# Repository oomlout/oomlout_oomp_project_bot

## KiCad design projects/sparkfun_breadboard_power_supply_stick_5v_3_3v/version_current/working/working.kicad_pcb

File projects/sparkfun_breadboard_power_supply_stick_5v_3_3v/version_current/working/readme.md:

# Breadboard_Power_Supply_Stick_5V-3.3V by sparkfun  
This is a harvested standardized copy of a project from github.  
The original project can be found at:  
https://github.com/sparkfun/Breadboard_Power_Supply_Stick_5V-3.3V  
Please consult that link for additional, details, files, and license information.  
Note: It was auto harvested and if the original repo had more than one board file or anything out of the ordinary the files here are likely not representative.

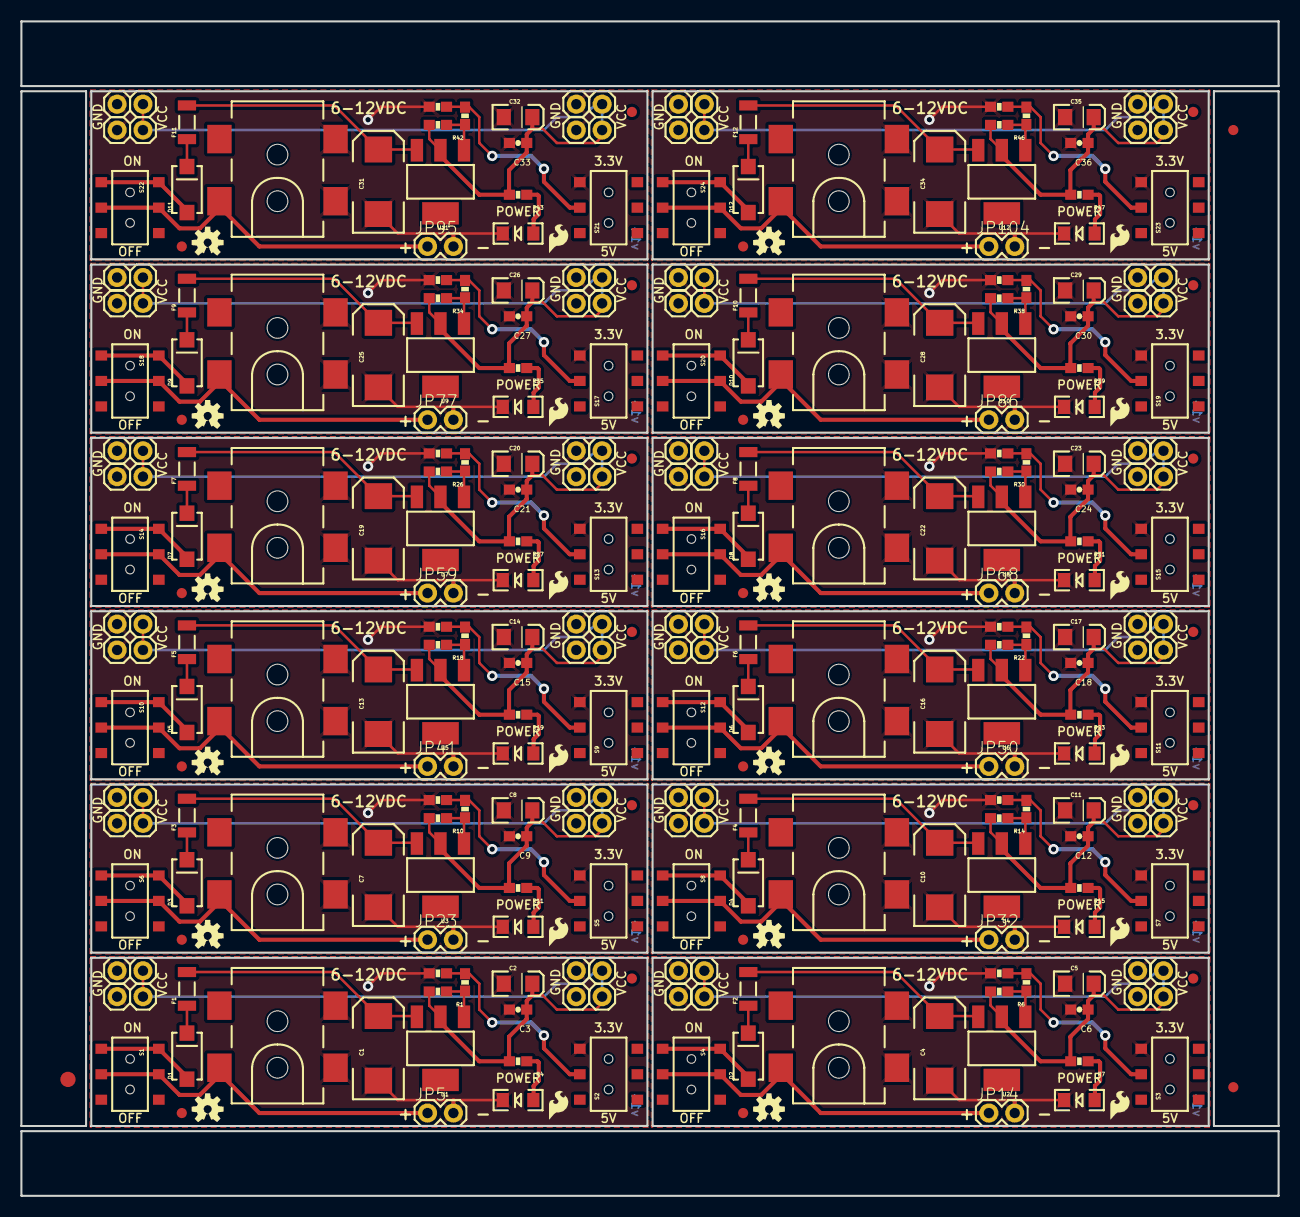
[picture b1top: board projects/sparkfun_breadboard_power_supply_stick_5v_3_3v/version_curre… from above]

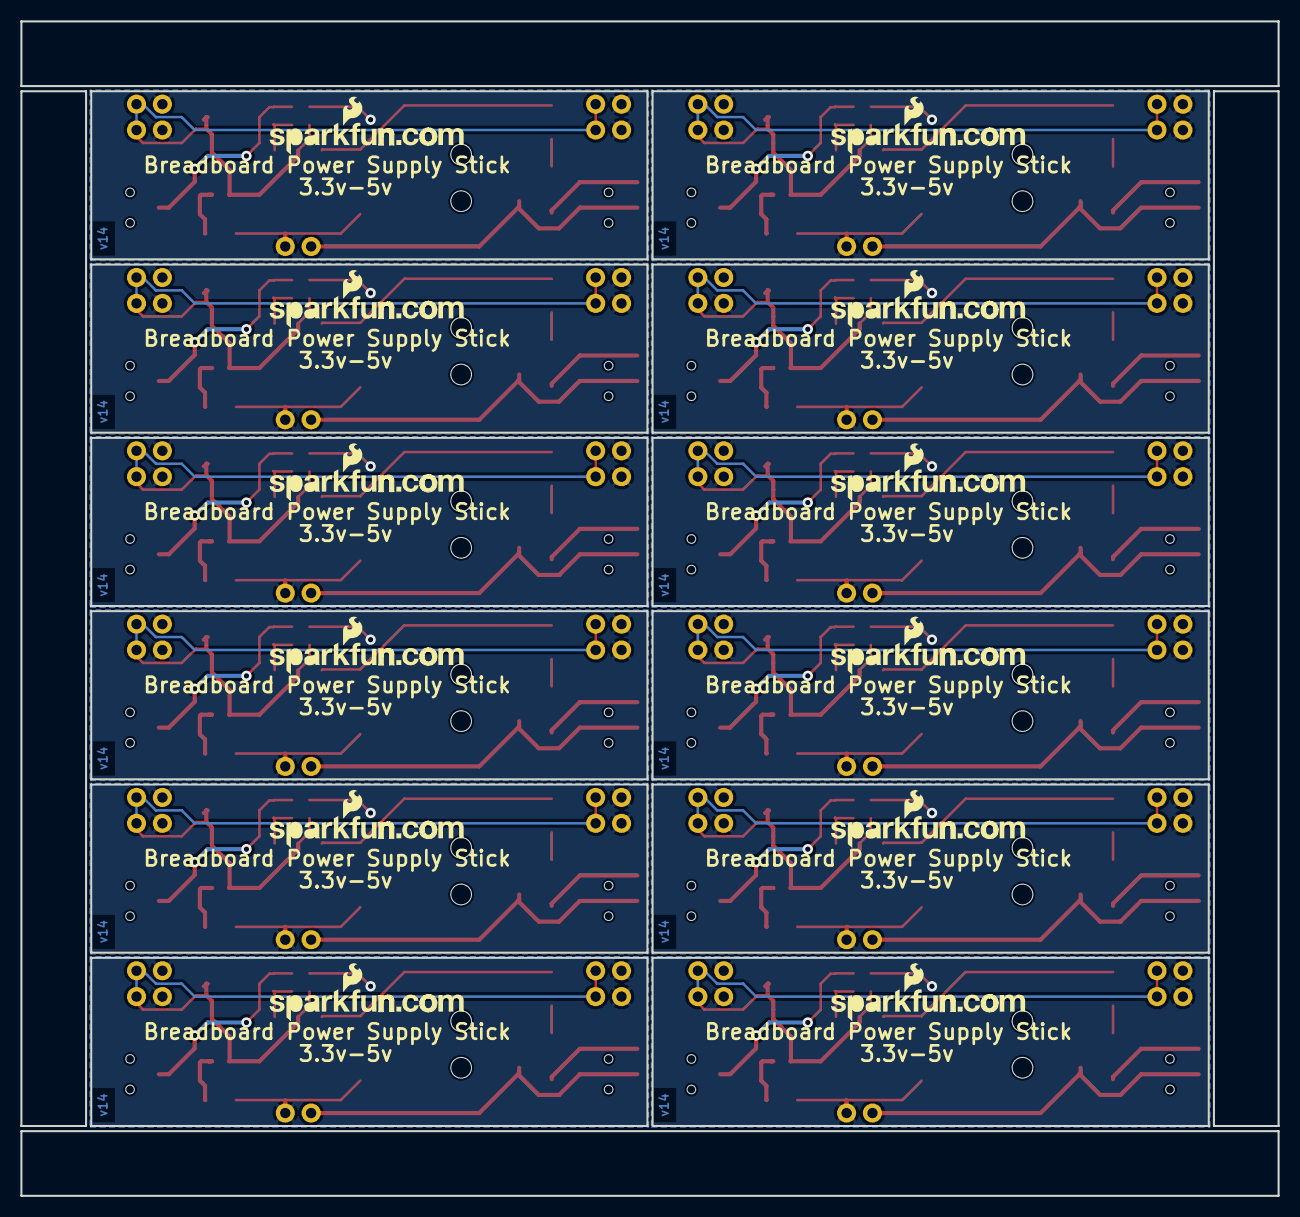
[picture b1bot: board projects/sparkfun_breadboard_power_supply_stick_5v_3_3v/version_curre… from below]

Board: 2 copper layers, 123.4 x 115.3 mm, 339 parts (12 on the bottom side), 108 nets.

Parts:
C1, C4, C7, C10, C13, C16, C19, C22, C25, C28, C31, C34: 100uF; EIA7343
C2, C5, C8, C11, C14, C17, C20, C23, C26, C29, C32, C35: 10uF; EIA3216
C3, C6, C9, C12, C15, C18, C21, C24, C27, C30, C33, C36: 0.1uF; 0603-CAP
D1, D2, D3, D4, D5, D6, D7, D8, D9, D10, D11, D12: 1N4001; SMA-DIODE-TYLERALT1
E$1: FIDUCIAL-1.5X3
E$4, E$6: FIDUCIAL-1X2
F1, F2, F3, F4, F5, F6, F7, F8, F9, F10, F11, F12: PTCSMD-W; PTC-1206-WIDE
J1, J2, J3, J4, J5, J6, J7, J8, J9, J10, J11, J12: 5.5x2.1mm Barrel; POWER_JACK_SMD
JP1, JP2, JP3, JP4, JP6, JP7, JP8, JP9, JP10, JP11, JP12, JP13, JP15, JP16, JP17, JP18, JP19, JP20, JP21, JP22, JP24, JP25, JP26, JP27, JP28, JP29, JP30, JP31, JP33, JP34, JP35, JP36, JP37, JP38, JP39, JP40, JP42, JP43, JP44, JP45, JP46, JP47, JP48, JP49, JP51, JP52, JP53, JP54, JP55, JP56, JP57, JP58, JP60, JP61, JP62, JP63, JP64, JP65, JP66, JP67, JP69, JP70, JP71, JP72, JP73, JP74, JP75, JP76, JP78, JP79, JP80, JP81, JP82, JP83, JP84, JP85, JP87, JP88, JP89, JP90, JP91, JP92, JP93, JP94, JP96, JP97, JP98, JP99, JP100, JP101, JP102, JP103, JP105, JP106, JP107, JP108: M01PTH; 1X01
JP5, JP14, JP23, JP32, JP41, JP50, JP59, JP68, JP77, JP86, JP95, JP104: 1X02
LED1, LED2, LED3, LED4, LED5, LED6, LED7, LED8, LED9, LED10, LED11, LED12: Power; LED-1206
LOGO1, LOGO2, LOGO3, LOGO4, LOGO5, LOGO6, LOGO7, LOGO8, LOGO9, LOGO10, LOGO11, LOGO12: OSHW-LOGOS; OSHW-LOGO-S
R1, R6, R10, R14, R18, R22, R26, R30, R34, R38, R42, R46: 240; 0603-RES
R2, R5, R9, R13, R17, R21, R25, R29, R33, R37, R41, R45: 390; 0603-RES
R3, R4, R7, R8, R11, R12, R15, R16, R19, R20, R23, R24, R27, R28, R31, R32, R35, R36, R39, R40, R43, R44, R47, R48: 330; 0603-RES
S1, S4, S6, S8, S10, S12, S14, S16, S18, S20, S22, S24: On/Off; AYZ0202
S2, S3, S5, S7, S9, S11, S13, S15, S17, S19, S21, S23: Voltage; AYZ0202
U1, U2, U3, U4, U5, U6, U7, U8, U9, U10, U11, U12: V_REG_317SMD; SOT223
U$1, U$5, U$9, U$13, U$17, U$21, U$25, U$29, U$33, U$37, U$41, U$45: LOGO-SFESK; SFE-LOGO-FLAME
U$2, U$6, U$10, U$14, U$18, U$22, U$26, U$30, U$34, U$38, U$42, U$46: LOGO-SFENEW; SFE-NEW-WEBLOGO
U$3, U$4, U$7, U$8, U$11, U$12, U$15, U$16, U$19, U$20, U$23, U$24, U$27, U$28, U$31, U$32, U$35, U$36, U$39, U$40, U$43, U$44, U$47, U$48: FIDUCIAL1X2; FIDUCIAL-1X2

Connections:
GND: C1.C, C2.C, C3.2, J1.GND, J1.P$4, JP1.1, JP4.1, JP5.2, JP6.1, JP9.1, LED2.C, R3.1, S2.3
GND1: C4.C, C5.C, C6.2, J2.GND, J2.P$4, JP10.1, JP13.1, JP14.2, JP15.1, JP18.1, LED1.C, R8.1, S3.3
GND2: C7.C, C8.C, C9.2, J3.GND, J3.P$4, JP19.1, JP22.1, JP23.2, JP24.1, JP27.1, LED3.C, R12.1, S5.3
GND3: C10.C, C11.C, C12.2, J4.GND, J4.P$4, JP28.1, JP31.1, JP32.2, JP33.1, JP36.1, LED4.C, R16.1, S7.3
GND4: C13.C, C14.C, C15.2, J5.GND, J5.P$4, JP37.1, JP40.1, JP41.2, JP42.1, JP45.1, LED5.C, R20.1, S9.3
GND5: C16.C, C17.C, C18.2, J6.GND, J6.P$4, JP46.1, JP49.1, JP50.2, JP51.1, JP54.1, LED6.C, R24.1, S11.3
GND6: C19.C, C20.C, C21.2, J7.GND, J7.P$4, JP55.1, JP58.1, JP59.2, JP60.1, JP63.1, LED7.C, R28.1, S13.3
GND7: C22.C, C23.C, C24.2, J8.GND, J8.P$4, JP64.1, JP67.1, JP68.2, JP69.1, JP72.1, LED8.C, R32.1, S15.3
GND8: C25.C, C26.C, C27.2, J9.GND, J9.P$4, JP73.1, JP76.1, JP77.2, JP78.1, JP81.1, LED9.C, R36.1, S17.3
GND9: C28.C, C29.C, C30.2, J10.GND, J10.P$4, JP82.1, JP85.1, JP86.2, JP87.1, JP90.1, LED10.C, R40.1, S19.3
GND10: C31.C, C32.C, C33.2, J11.GND, J11.P$4, JP91.1, JP94.1, JP95.2, JP96.1, JP99.1, LED11.C, R44.1, S21.3
GND11: C34.C, C35.C, C36.2, J12.GND, J12.P$4, JP100.1, JP103.1, JP104.2, JP105.1, JP108.1, LED12.C, R48.1, S23.3
unnamed: D1.C, F1.1
unnamed: D1.A, S1.1, S1.4
unnamed: R5.2, R6.1, U2.1
unnamed: R2.1, R3.2, S2.2
unnamed: R1.1, R2.2, U1.1
unnamed: LED1.A, R7.1
unnamed: D2.C, F2.1
unnamed: LED2.A, R4.1
unnamed: D2.A, S4.1, S4.4
unnamed: R5.1, R8.2, S3.2
unnamed: R9.2, R10.1, U3.1
unnamed: LED3.A, R11.1
unnamed: D3.C, F3.1
unnamed: D3.A, S6.1, S6.4
unnamed: R9.1, R12.2, S5.2
unnamed: R13.2, R14.1, U4.1
unnamed: LED4.A, R15.1
unnamed: D4.C, F4.1
unnamed: D4.A, S8.1, S8.4
unnamed: R13.1, R16.2, S7.2
unnamed: R17.2, R18.1, U5.1
unnamed: LED5.A, R19.1
unnamed: D5.C, F5.1
unnamed: D5.A, S10.1, S10.4
unnamed: R17.1, R20.2, S9.2
unnamed: R21.2, R22.1, U6.1
unnamed: LED6.A, R23.1
unnamed: D6.C, F6.1
unnamed: D6.A, S12.1, S12.4
unnamed: R21.1, R24.2, S11.2
unnamed: R25.2, R26.1, U7.1
unnamed: LED7.A, R27.1
unnamed: D7.C, F7.1
unnamed: D7.A, S14.1, S14.4
unnamed: R25.1, R28.2, S13.2
unnamed: R29.2, R30.1, U8.1
unnamed: LED8.A, R31.1
unnamed: D8.C, F8.1
unnamed: D8.A, S16.1, S16.4
unnamed: R29.1, R32.2, S15.2
unnamed: R33.2, R34.1, U9.1
unnamed: LED9.A, R35.1
unnamed: D9.C, F9.1
unnamed: D9.A, S18.1, S18.4
unnamed: R33.1, R36.2, S17.2
unnamed: R37.2, R38.1, U10.1
unnamed: LED10.A, R39.1
unnamed: D10.C, F10.1
unnamed: D10.A, S20.1, S20.4
unnamed: R37.1, R40.2, S19.2
unnamed: R41.2, R42.1, U11.1
unnamed: LED11.A, R43.1
unnamed: D11.C, F11.1
unnamed: D11.A, S22.1, S22.4
unnamed: R41.1, R44.2, S21.2
unnamed: R45.2, R46.1, U12.1
unnamed: LED12.A, R47.1
unnamed: D12.C, F12.1
unnamed: D12.A, S24.1, S24.4
unnamed: R45.1, R48.2, S23.2
RAW: C1.A, F1.2, U1.3
RAW1: C4.A, F2.2, U2.3
RAW2: C7.A, F3.2, U3.3
RAW3: C10.A, F4.2, U4.3
RAW4: C13.A, F5.2, U5.3
RAW5: C16.A, F6.2, U6.3
RAW6: C19.A, F7.2, U7.3
RAW7: C22.A, F8.2, U8.3
RAW8: C25.A, F9.2, U9.3
RAW9: C28.A, F10.2, U10.3
RAW10: C31.A, F11.2, U11.3
RAW11: C34.A, F12.2, U12.3
VCC: C2.A, C3.1, JP2.1, JP3.1, JP7.1, JP8.1, R1.2, R4.2, U1.2
VCC1: C5.A, C6.1, JP11.1, JP12.1, JP16.1, JP17.1, R6.2, R7.2, U2.2
VCC2: C8.A, C9.1, JP20.1, JP21.1, JP25.1, JP26.1, R10.2, R11.2, U3.2
VCC3: C11.A, C12.1, JP29.1, JP30.1, JP34.1, JP35.1, R14.2, R15.2, U4.2
VCC4: C14.A, C15.1, JP38.1, JP39.1, JP43.1, JP44.1, R18.2, R19.2, U5.2
VCC5: C17.A, C18.1, JP47.1, JP48.1, JP52.1, JP53.1, R22.2, R23.2, U6.2
VCC6: C20.A, C21.1, JP56.1, JP57.1, JP61.1, JP62.1, R26.2, R27.2, U7.2
VCC7: C23.A, C24.1, JP65.1, JP66.1, JP70.1, JP71.1, R30.2, R31.2, U8.2
VCC8: C26.A, C27.1, JP74.1, JP75.1, JP79.1, JP80.1, R34.2, R35.2, U9.2
VCC9: C29.A, C30.1, JP83.1, JP84.1, JP88.1, JP89.1, R38.2, R39.2, U10.2
VCC10: C32.A, C33.1, JP92.1, JP93.1, JP97.1, JP98.1, R42.2, R43.2, U11.2
VCC11: C35.A, C36.1, JP101.1, JP102.1, JP106.1, JP107.1, R46.2, R47.2, U12.2
VIN: J1.VIN0, JP5.1, S1.2, S1.5
VIN1: J2.VIN0, JP14.1, S4.2, S4.5
VIN2: J3.VIN0, JP23.1, S6.2, S6.5
VIN3: J4.VIN0, JP32.1, S8.2, S8.5
VIN4: J5.VIN0, JP41.1, S10.2, S10.5
VIN5: J6.VIN0, JP50.1, S12.2, S12.5
VIN6: J7.VIN0, JP59.1, S14.2, S14.5
VIN7: J8.VIN0, JP68.1, S16.2, S16.5
VIN8: J9.VIN0, JP77.1, S18.2, S18.5
VIN9: J10.VIN0, JP86.1, S20.2, S20.5
VIN10: J11.VIN0, JP95.1, S22.2, S22.5
VIN11: J12.VIN0, JP104.1, S24.2, S24.5

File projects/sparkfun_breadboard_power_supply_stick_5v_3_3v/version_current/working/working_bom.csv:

Row,Description,Part,References,Value,Footprint,Quantity Per PCB,Status,Datasheet
1,,CAP0603-CAP,C3,0.1uF,0603-CAP,1, ,
2,,CAP_POL1206,C2,10uF,EIA3216,1, ,
3,,CAP_POL7343,C1,100uF,EIA7343,1, ,
4,,DIODESMA-TYLERALT1,D1,1N4001,SMA-DIODE-TYLERALT1,1, ,
5,,PTCSMD-W,F1,PTCSMD-W,PTC-1206-WIDE,1, ,
6,,FRAME-LETTER,FRAME1,FRAME-LETTER,CREATIVE_COMMONS,1, ,
7,,POWER_JACKSMD,J1,POWER_JACKSMD,POWER_JACK_SMD,1, ,
8,,M01PTH,JP1 JP2 JP3 JP4 JP6 JP7 JP8 JP9,M01PTH,1X01,8, ,
9,,M02PTH,JP5,M02PTH,1X02,1, ,
10,,LED1206,LED2,Power,LED-1206,1, ,
11,,OSHW-LOGOS,LOGO1,OSHW-LOGOS,OSHW-LOGO-S,1, ,
12,,RESISTOR0603-RES,R1,240,0603-RES,1, ,
13,,RESISTOR0603-RES,R3 R4,330,0603-RES,2, ,
14,,RESISTOR0603-RES,R2,390,0603-RES,1, ,
15,,AYZ0202,S1,AYZ0202,AYZ0202,1, ,
16,,SWITCH-SPSTSMD,S2,Voltage,AYZ0202,1, ,
17,,V_REG_317SMD,U1,V_REG_317SMD,SOT223,1, ,
18,,LOGO-SFENEW,U$2,LOGO-SFENEW,SFE-NEW-WEBLOGO,1, ,
19,,LOGO-SFESK,U$1,LOGO-SFESK,SFE-LOGO-FLAME,1, ,





Project info:
Schematic:,working
Variant:,default
Revision:,
Date:,2023-08-06_12-56-00
KiCad Version:,7.0.6-7.0.6~ubuntu22.04.1
Statistics:
Component Groups:,19
Component Count:,27 (0 SMD/ 0 THT)
Fitted Components:,27 (0 SMD/ 0 THT)
Number of PCBs:,1
Total Components:,27

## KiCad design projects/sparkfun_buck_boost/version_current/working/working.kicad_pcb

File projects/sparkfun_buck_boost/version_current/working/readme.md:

# Buck-Boost by sparkfun  
This is a harvested standardized copy of a project from github.  
The original project can be found at:  
https://github.com/sparkfun/Buck-Boost  
Please consult that link for additional, details, files, and license information.  
Note: It was auto harvested and if the original repo had more than one board file or anything out of the ordinary the files here are likely not representative.

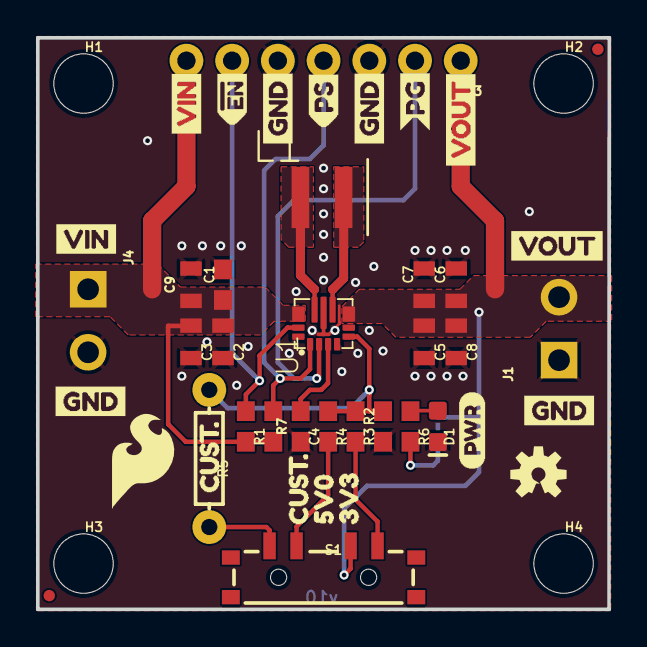
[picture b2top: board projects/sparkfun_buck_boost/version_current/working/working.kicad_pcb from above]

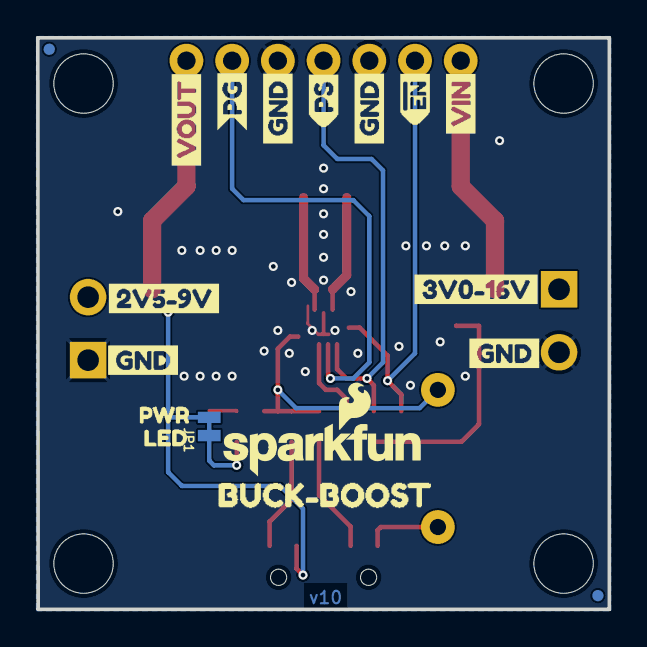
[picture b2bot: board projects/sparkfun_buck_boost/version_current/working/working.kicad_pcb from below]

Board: 2 copper layers, 31.8 x 31.8 mm, 67 parts (18 on the bottom side), 15 nets.

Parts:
C1, C4: 0.1uF; 0603
C2, C3, C5, C9: 10uF; 0805
C6, C7, C8: 22uF; 0805
D1: RED; LED-0603
FD1, FD2, FD3, FD4: FIDUCIALUFIDUCIAL; FIDUCIAL-MICRO
FRAME1: FRAME-LETTER; CREATIVE_COMMONS
H1, H2, H3, H4: STAND-OFF
J1, J4: SCREWTERMINAL-3.5MM-2-NS
J3: 1X07_NO_SILK
JP1: SMT-JUMPER_2_NC_TRACE_NO-SILK
L1: 1.5uH; XFL4020
LOGO1: SFE_LOGO_NAME_FLAME.1_INCH; SFE_LOGO_NAME_FLAME_.1
LOGO2: OSHW-LOGOS; OSHW-LOGO-S
LOGO3: SPECIAL_INSTRUCTIONS-ORDERING; ORDERING_INSTRUCTIONS
R1, R7: 10k; 0603
R2: 68.1k; 0603
R3: 213k; 0603
R4: 365k; 0603
R5: CUSTOM; AXIAL-0.3
R6: 1k; 0603
S1: SWITCH_SP3T_SMD
U1: TPS63070; VQFN-15-HR(3X2.5)
U$1: PWR2
U$2, U$17: CUST#7
U$3, U$25: VIN0
U$4, U$20, U$30, U$31: GND1
U$5: VIN3
U$6, U$7, U$12, U$13: GND4
U$8: VOUT5
U$9: SFE_LOGO_FLAME_.2
U$10: 3V0#16V6
U$11: PWR1
U$14: 2V5#9V1
U$15: BUCK#BOOST18
U$16: LED0
U$18: 5V08
U$19: 3V39
U$21, U$26: VOUT2
U$22, U$28: #EN0
U$23, U$29: PS1
U$24, U$27: PG2

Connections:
FB: R2.2, R3.1, R4.1, R5.P$1, U1.P$5
GND: C1.2, C2.2, C3.2, C4.2, C5.2, C6.2, C7.2, C8.2, C9.2, D1.C, J1.1, J3.3, J3.5, J4.2, R2.1, U1.P$4, U1.P$6, U1.P$10, U1.P$15
unnamed: L1.P$1, U1.P$11
unnamed: L1.P$2, U1.P$9
unnamed: R5.P$2, S1.1
unnamed: R4.2, S1.2
unnamed: C4.1, U1.P$3
unnamed: R3.2, S1.4
unnamed: JP1.1, R6.2
unnamed: D1.A, R6.1
PG: J3.2, U1.P$2
PS: J3.4, R7.1, U1.P$1
VIN: C1.1, C2.1, C3.1, C9.1, J3.7, J4.1, R1.2, R7.2, U1.P$12/13
VOUT: C5.1, C6.1, C7.1, C8.1, J1.2, J3.1, JP1.2, S1.3, U1.P$7/8
~EN: J3.6, R1.1, U1.P$14

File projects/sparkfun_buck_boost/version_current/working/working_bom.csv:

"Id";"Designator";"Footprint";"Quantity";"Designation";"Supplier and ref";
1;"U$21,U$26";"VOUT2";2;"";;;
2;"C8,C6,C7";"0805";3;"22uF";;;
3;"LOGO2";"OSHW-LOGO-S";1;"OSHW-LOGOS";;;
4;"C9,C2,C3,C5";"0805";4;"10uF";;;
5;"U$20,U$4,U$30,U$31";"GND1";4;"";;;
6;"J1,J4";"SCREWTERMINAL-3.5MM-2-NS";2;"";;;
7;"C4,C1";"0603";2;"0.1uF";;;
8;"L1";"XFL4020";1;"1.5uH";;;
9;"U$23,U$29";"PS1";2;"";;;
10;"R4";"0603";1;"365k";;;
11;"U$7,U$6,U$13,U$12";"GND4";4;"";;;
12;"FD3,FD1,FD2,FD4";"FIDUCIAL-MICRO";4;"FIDUCIALUFIDUCIAL";;;
13;"FRAME1";"CREATIVE_COMMONS";1;"FRAME-LETTER";;;
14;"H3,H2,H1,H4";"STAND-OFF";4;"STAND-OFF";;;
15;"U$8";"VOUT5";1;"";;;
16;"R5";"AXIAL-0.3";1;"CUSTOM";;;
17;"U$2,U$17";"CUST#7";2;"";;;
18;"U$18";"5V08";1;"";;;
19;"U1";"VQFN-15-HR(3X2.5)";1;"TPS63070";;;
20;"U$19";"3V39";1;"";;;
21;"D1";"LED-0603";1;"RED";;;
22;"R2";"0603";1;"68.1k";;;
23;"LOGO3";"ORDERING_INSTRUCTIONS";1;"SPECIAL_INSTRUCTIONS-ORDERING";;;
24;"R3";"0603";1;"213k";;;
25;"U$3,U$25";"VIN0";2;"";;;
26;"R6";"0603";1;"1k";;;
27;"U$5";"VIN3";1;"";;;
28;"S1";"SWITCH_SP3T_SMD";1;"";;;
29;"R7,R1";"0603";2;"10k";;;
30;"U$9";"SFE_LOGO_FLAME_.2";1;"";;;
31;"J3";"1X07_NO_SILK";1;"";;;
32;"U$1";"PWR2";1;"";;;
33;"U$24,U$27";"PG2";2;"";;;
34;"U$22,U$28";"#EN0";2;"";;;
35;"U$16";"LED0";1;"";;;
36;"JP1";"SMT-JUMPER_2_NC_TRACE_NO-SILK";1;"";;;
37;"LOGO1";"SFE_LOGO_NAME_FLAME_.1";1;"SFE_LOGO_NAME_FLAME.1_INCH";;;
38;"U$10";"3V0#16V6";1;"";;;
39;"U$11";"PWR1";1;"";;;
40;"U$15";"BUCK#BOOST18";1;"";;;
41;"U$14";"2V5#9V1";1;"";;;

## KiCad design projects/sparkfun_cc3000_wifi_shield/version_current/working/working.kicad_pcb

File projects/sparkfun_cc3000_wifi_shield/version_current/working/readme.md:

# OOMP Project  
## CC3000_WiFi_Shield  by sparkfun  
  
oomp key: oomp_projects_flat_sparkfun_cc3000_wifi_shield  
(snippet of original readme)  
  
CC3000_WiFi_Shield  
====================  
  
[    
*CC3000 WiFi Shield (WRL-12071)*](https://www.sparkfun.com/products/12071)  
  
Arduino WiFi shield for the [TI CC3000 module](http://www.ti.com/product/cc3000). The datasheet can be found [here](http://www.ti.com/lit/ds/symlink/cc3000.pdf).  
  
Arduino library and examples can be found in the [SFE_CC3000_Library](https://github.com/sparkfun/SFE_CC3000_Library).  
  
This part was created in Eagle v6.5.0. Example sketches were created in Arduino v1.0.5.  
  
Repository Contents  
-------------------  
  
* **/Hardware** - All Eagle design files (.brd, .sch, .STL)  
* **/Production** - Test bed files and production panel files  
  
Version History  
---------------  
* **v1.0** Initial release  
  
License Information  
-------------------  
The hardware is released under [Creative Commons Share-alike 3.0](http://creativecommons.org/licenses/by-sa/3.0/).    
All other code is open source so please feel free to do anything you want with it; you buy me a beer if you use this and we meet someday ([Beerware license](http://en.wikipedia.org/wiki/Beerware)).  
  full source readme at [readme_src.md](readme_src.md)  
  
source repo at: [https://github.com/sparkfun/CC3000_WiFi_Shield](https://github.com/sparkfun/CC3000_WiFi_Shield)  
## Board  

## Schematic  

[schematic pdf](working_schematic.pdf)  
## Images

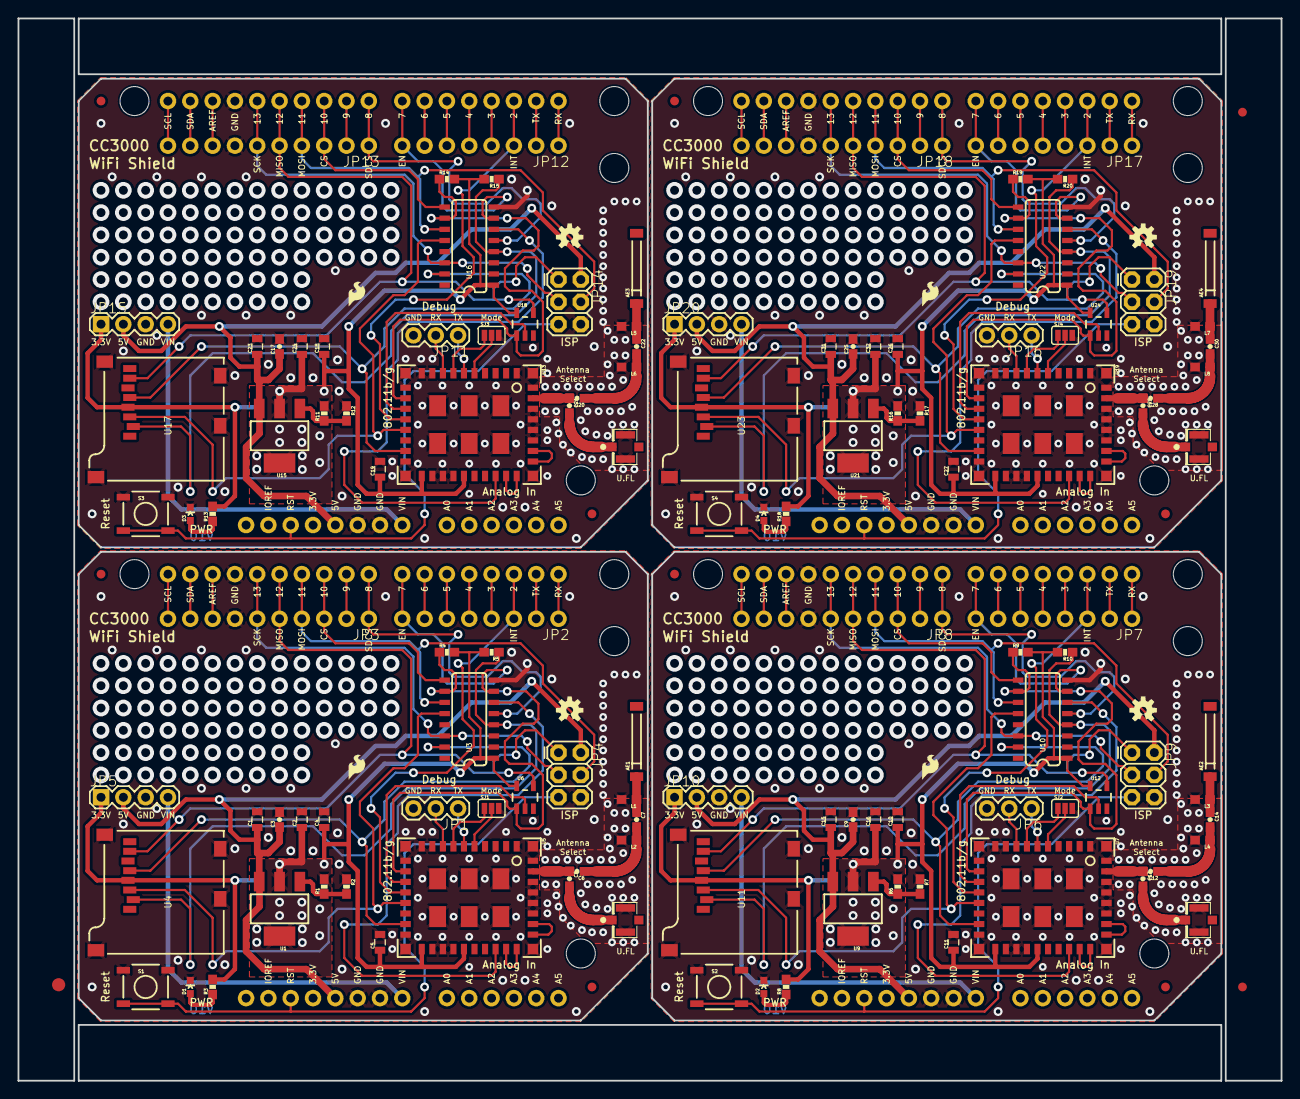
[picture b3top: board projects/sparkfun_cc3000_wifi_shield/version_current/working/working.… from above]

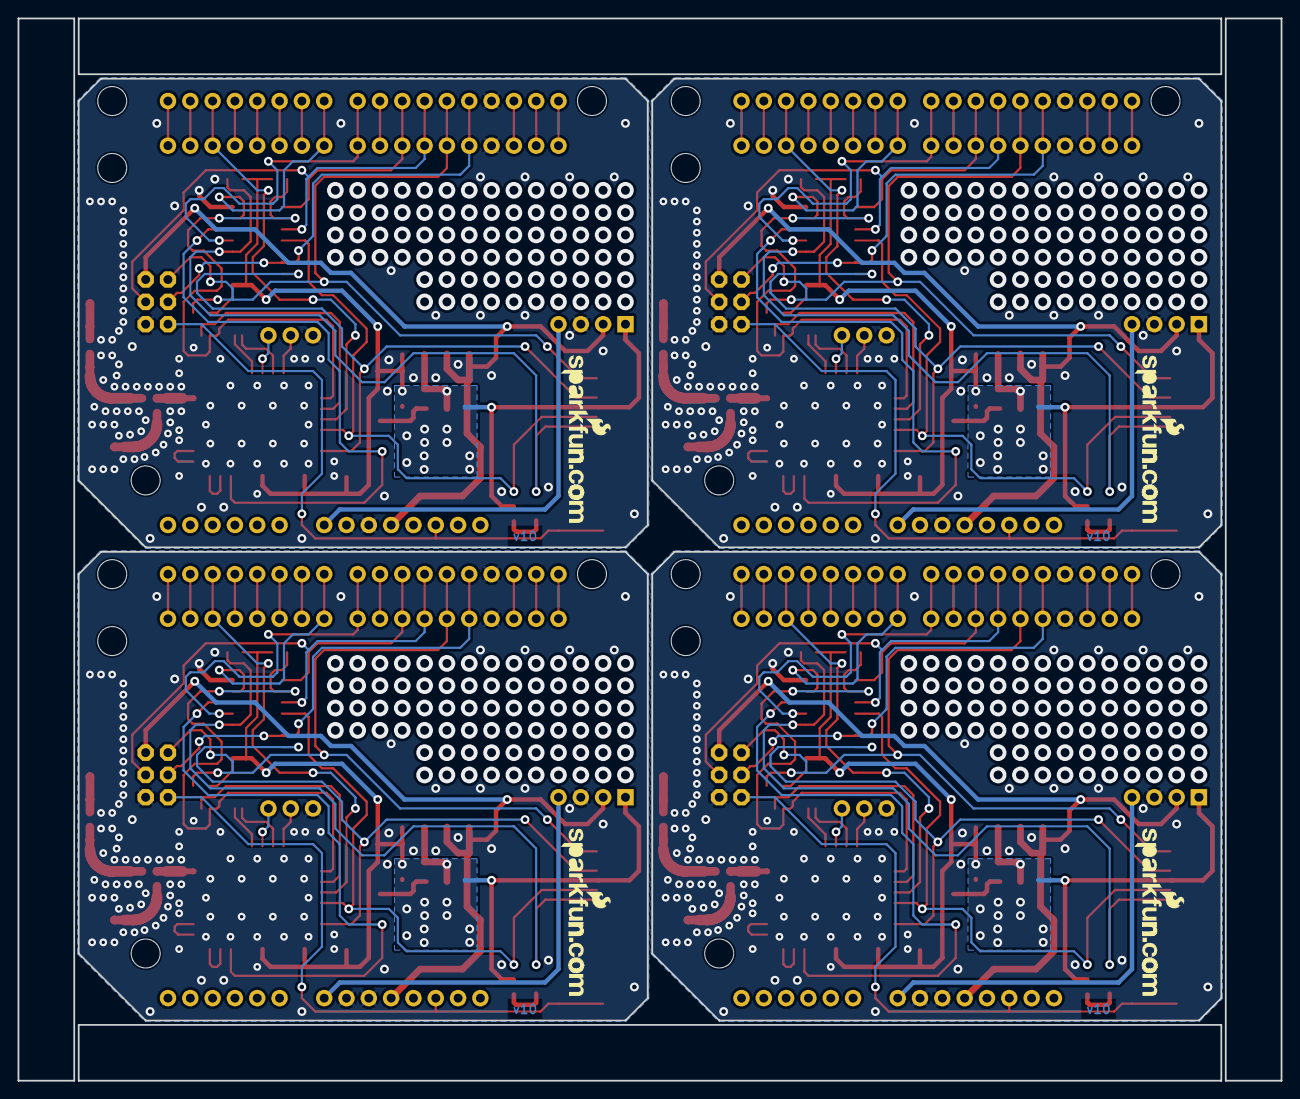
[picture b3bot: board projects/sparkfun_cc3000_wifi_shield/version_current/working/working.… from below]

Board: 4 copper layers, 143.8 x 120.9 mm, 163 parts (4 on the bottom side), 160 nets.

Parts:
@HOLE0, @HOLE1, @HOLE2, @HOLE3, @HOLE4, @HOLE5, @HOLE6, @HOLE7: (no value)
AE1, AE2, AE3, AE4: ANTENNA22500AT44M0400; ANTENNA-CHIP_2500AT44M0400
C1, C2, C15, C16, C23, C24, C31, C32: 10uF; 0805
C3, C9, C17, C25: 0.1uF; 0603-CAP
C4, C5, C10, C11, C18, C19, C26, C27: 1uF; 0805
C6, C12, C20, C28: 10pF; 0603-CAP
C7, C14, C22, C30: 2.2pF; 0603-CAP
C8, C13, C21, C29: DNP; 0603-CAP
D1, D2, D3, D4: GREEN; LED-0603
E$1: FIDUCIAL-1.5X3
E$4, E$5: FIDUCIAL-1X2
FID1, FID2, FID3, FID4, FID5, FID6, FID7, FID8: FIDUCIAL1X2; FIDUCIAL-1X2
J1, J2, J3, J4: U.FL
JP1, JP6, JP11, JP16: Debug; 1X03
JP2, JP7, JP12, JP17: 1X08_NO_SILK
JP3, JP8, JP13, JP18: M10NO_SILK; 1X10_NO_SILK
JP4, JP9, JP14, JP19: AVR_SPI_PRG_6PTH; 2X3
JP5, JP10, JP15, JP20: 1X04
L1, L3, L5, L7: DNP; 0603
L2, L4, L6, L8: 2.2nH; 0603
LOGO1, LOGO4, LOGO7, LOGO10: OSHW-LOGOS; OSHW-LOGO-S
LOGO2, LOGO5, LOGO8, LOGO11: LOGO-SFENEW; SFE-NEW-WEBLOGO
LOGO3, LOGO6, LOGO9, LOGO12: LOGO-SFESK; SFE-LOGO-FLAME
R1, R6, R11, R16: 240; 0603-RES
R2, R3, R7, R8, R12, R13, R17, R18: 390; 0603-RES
R4, R5, R9, R10, R14, R15, R19, R20: 10k; 0603-RES
S1, S2, S3, S4: RESET; TACTILE_SWITCH_SMD
SJ1, SJ2, SJ3, SJ4: Mode; SJ_3_PASTE1&2
STANDOFF1, STANDOFF2, STANDOFF3, STANDOFF4, STANDOFF5, STANDOFF6, STANDOFF7, STANDOFF8: STAND-OFF
U1, U9, U15, U21: LM1117; SOT223
U2, U8, U14, U20: ARDUINO_R3_SHIELDNOLABELS; UNO_R3_SHIELD_NOLABELS
U3, U10, U16, U22: 74HC4050; SO016
U4, U11, U17, U23: USD-SOCKETNEW; MICRO-SD-SOCKET-PP
U5, U7, U13, U19: CC3000; QFN-46_CC3000
U6, U12, U18, U24: 74AHC1G125; SOT23-5

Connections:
3.3V: C2.1, C4.1, C5.1, JP5.1, R1.2, R3.2, R4.2, R5.2, U1.2, U1.4, U3.1, U4.4, U5.P$19, U5.P$23, U6.5
3.3V1: C10.1, C11.1, C16.1, JP10.1, R6.2, R8.2, R9.2, R10.2, U7.P$19, U7.P$23, U9.2, U9.4, U10.1, U11.4, U12.5
3.3V2: C18.1, C19.1, C24.1, JP15.1, R11.2, R13.2, R14.2, R15.2, U13.P$19, U13.P$23, U15.2, U15.4, U16.1, U17.4, U18.5
3.3V3: C26.1, C27.1, C32.1, JP20.1, R16.2, R18.2, R19.2, R20.2, U19.P$19, U19.P$23, U21.2, U21.4, U22.1, U23.4, U24.5
5V: C1.1, C3.1, JP4.2, JP5.2, U1.3, U2.5V
5V1: C9.1, C15.1, JP9.2, JP10.2, U8.5V, U9.3
5V2: C17.1, C23.1, JP14.2, JP15.2, U14.5V, U15.3
5V3: C25.1, C31.1, JP19.2, JP20.2, U20.5V, U21.3
AREF: JP3.8, U2.AREF
AREF1: JP8.8, U8.AREF
AREF2: JP13.8, U14.AREF
AREF3: JP18.8, U20.AREF
CS_3.3V: R4.1, U3.10, U5.P$12, U6.1
CS_3.3V1: R9.1, U7.P$12, U10.10, U12.1
CS_3.3V2: R14.1, U13.P$12, U16.10, U18.1
CS_3.3V3: R19.1, U19.P$12, U22.10, U24.1
CS_5V: JP3.3, U2.D10, U3.9
CS_5V1: JP8.3, U8.D10, U10.9
CS_5V2: JP13.3, U14.D10, U16.9
CS_5V3: JP18.3, U20.D10, U22.9
EN_3.3V: U3.6, U5.P$26
EN_3.3V1: U7.P$26, U10.6
EN_3.3V2: U13.P$26, U16.6
EN_3.3V3: U19.P$26, U22.6
EN_5V: JP2.8, U2.D7, U3.7
EN_5V1: JP7.8, U8.D7, U10.7
EN_5V2: JP12.8, U14.D7, U16.7
EN_5V3: JP17.8, U20.D7, U22.7
GND: C1.2, C2.2, C3.2, C4.2, C5.2, D1.C, J1.P$1, J1.P$2, JP1.3, JP3.7, JP4.6, JP5.3, L1.2, L2.2, R2.1, S1.1, S1.2, SJ1.3, U2.GND@0, U2.GND@1, U2.GND@2, U3.8, U4.6, U4.CD1, U4.CD2, U4.GND1, U4.GND3, U5.GND@37, U5.GND@38, U5.GND@39, U5.GND@40, U5.GND@41, U5.GND@42, U5.GND@43, U5.GND@44, U5.GND@45, U5.GND@46, U5.P$1, U5.P$9, U5.P$10, U5.P$11, U5.P$16, U5.P$18, U5.P$20, U5.P$21, U5.P$22, U5.P$25, U5.P$31, U5.P$32, U5.P$33, U5.P$34, U5.P$36, U6.3
GND1: C9.2, C10.2, C11.2, C15.2, C16.2, D2.C, J2.P$1, J2.P$2, JP6.3, JP8.7, JP9.6, JP10.3, L3.2, L4.2, R7.1, S2.1, S2.2, SJ2.3, U7.GND@37, U7.GND@38, U7.GND@39, U7.GND@40, U7.GND@41, U7.GND@42, U7.GND@43, U7.GND@44, U7.GND@45, U7.GND@46, U7.P$1, U7.P$9, U7.P$10, U7.P$11, U7.P$16, U7.P$18, U7.P$20, U7.P$21, U7.P$22, U7.P$25, U7.P$31, U7.P$32, U7.P$33, U7.P$34, U7.P$36, U8.GND@0, U8.GND@1, U8.GND@2, U10.8, U11.6, U11.CD1, U11.CD2, U11.GND1, U11.GND3, U12.3
GND2: C17.2, C18.2, C19.2, C23.2, C24.2, D3.C, J3.P$1, J3.P$2, JP11.3, JP13.7, JP14.6, JP15.3, L5.2, L6.2, R12.1, S3.1, S3.2, SJ3.3, U13.GND@37, U13.GND@38, U13.GND@39, U13.GND@40, U13.GND@41, U13.GND@42, U13.GND@43, U13.GND@44, U13.GND@45, U13.GND@46, U13.P$1, U13.P$9, U13.P$10, U13.P$11, U13.P$16, U13.P$18, U13.P$20, U13.P$21, U13.P$22, U13.P$25, U13.P$31, U13.P$32, U13.P$33, U13.P$34, U13.P$36, U14.GND@0, U14.GND@1, U14.GND@2, U16.8, U17.6, U17.CD1, U17.CD2, U17.GND1, U17.GND3, U18.3
GND3: C25.2, C26.2, C27.2, C31.2, C32.2, D4.C, J4.P$1, J4.P$2, JP16.3, JP18.7, JP19.6, JP20.3, L7.2, L8.2, R17.1, S4.1, S4.2, SJ4.3, U19.GND@37, U19.GND@38, U19.GND@39, U19.GND@40, U19.GND@41, U19.GND@42, U19.GND@43, U19.GND@44, U19.GND@45, U19.GND@46, U19.P$1, U19.P$9, U19.P$10, U19.P$11, U19.P$16, U19.P$18, U19.P$20, U19.P$21, U19.P$22, U19.P$25, U19.P$31, U19.P$32, U19.P$33, U19.P$34, U19.P$36, U20.GND@0, U20.GND@1, U20.GND@2, U22.8, U23.6, U23.CD1, U23.CD2, U23.GND1, U23.GND3, U24.3
INT_3.3V: JP2.3, U2.D2, U5.P$14
INT_3.3V1: JP7.3, U7.P$14, U8.D2
INT_3.3V2: JP12.3, U13.P$14, U14.D2
INT_3.3V3: JP17.3, U19.P$14, U20.D2
MISO_3.3V: JP3.5, JP4.1, U2.D12, U4.7, U6.4
MISO_3.3V1: JP8.5, JP9.1, U8.D12, U11.7, U12.4
MISO_3.3V2: JP13.5, JP14.1, U14.D12, U17.7, U18.4
MISO_3.3V3: JP18.5, JP19.1, U20.D12, U23.7, U24.4
MOSI_3.3V: U3.12, U4.3, U5.P$15
MOSI_3.3V1: U7.P$15, U10.12, U11.3
MOSI_3.3V2: U13.P$15, U16.12, U17.3
MOSI_3.3V3: U19.P$15, U22.12, U23.3
MOSI_5V: JP3.4, JP4.4, U2.D11, U3.11
MOSI_5V1: JP8.4, JP9.4, U8.D11, U10.11
MOSI_5V2: JP13.4, JP14.4, U14.D11, U16.11
MOSI_5V3: JP18.4, JP19.4, U20.D11, U22.11
unnamed: R6.1, R7.2, U9.1
unnamed: R1.1, R2.2, U1.1
unnamed: SJ1.2, U5.P$5
unnamed: SJ1.1, U5.P$7
unnamed: C6.1, C7.2, L2.1
unnamed: U5.P$27, U5.P$28
unnamed: U5.P$29, U5.P$30
unnamed: C6.2, C8.1, U5.P$35
unnamed: C8.2, J1.P$3
unnamed: AE1.FEED, C7.1, L1.1
unnamed: D1.A, R3.1
unnamed: SJ2.2, U7.P$5
unnamed: SJ2.1, U7.P$7
unnamed: U7.P$27, U7.P$28
unnamed: U7.P$29, U7.P$30
unnamed: C12.1, C14.2, L4.1
unnamed: AE2.FEED, C14.1, L3.1
unnamed: C13.2, J2.P$3
unnamed: D2.A, R8.1
unnamed: JP2.1, U2.RX
unnamed: JP2.2, U2.TX
unnamed: JP2.4, U2.D3
unnamed: JP2.6, U2.D5
unnamed: JP2.7, U2.D6
unnamed: JP2.5, U2.D4
unnamed: JP3.2, U2.D9
unnamed: C12.2, C13.1, U7.P$35
unnamed: JP7.4, U8.D3
unnamed: JP7.6, U8.D5
unnamed: JP7.7, U8.D6
unnamed: JP7.1, U8.RX
unnamed: JP7.2, U8.TX
unnamed: JP8.2, U8.D9
unnamed: JP7.5, U8.D4
unnamed: R11.1, R12.2, U15.1
unnamed: SJ3.2, U13.P$5
unnamed: SJ3.1, U13.P$7
unnamed: U13.P$27, U13.P$28
unnamed: U13.P$29, U13.P$30
unnamed: C20.1, C22.2, L6.1
unnamed: AE3.FEED, C22.1, L5.1
unnamed: C21.2, J3.P$3
unnamed: D3.A, R13.1
unnamed: C20.2, C21.1, U13.P$35
unnamed: JP12.4, U14.D3
unnamed: JP12.6, U14.D5
unnamed: JP12.7, U14.D6
unnamed: JP12.1, U14.RX
unnamed: JP12.2, U14.TX
unnamed: JP13.2, U14.D9
unnamed: JP12.5, U14.D4
unnamed: R16.1, R17.2, U21.1
unnamed: SJ4.2, U19.P$5
unnamed: SJ4.1, U19.P$7
unnamed: U19.P$27, U19.P$28
unnamed: U19.P$29, U19.P$30
unnamed: C28.1, C30.2, L8.1
unnamed: AE4.FEED, C30.1, L7.1
unnamed: C29.2, J4.P$3
unnamed: D4.A, R18.1
unnamed: C28.2, C29.1, U19.P$35
unnamed: JP17.4, U20.D3
unnamed: JP17.6, U20.D5
unnamed: JP17.7, U20.D6
unnamed: JP17.1, U20.RX
unnamed: JP17.2, U20.TX
unnamed: JP18.2, U20.D9
unnamed: JP17.5, U20.D4
RESET: JP4.5, S1.3, S1.4, U2.RES
RESET1: JP9.5, S2.3, S2.4, U8.RES
RESET2: JP14.5, S3.3, S3.4, U14.RES
RESET3: JP19.5, S4.3, S4.4, U20.RES
SCK_3.3V: U3.15, U4.5, U5.P$17
SCK_3.3V1: U7.P$17, U10.15, U11.5
SCK_3.3V2: U13.P$17, U16.15, U17.5
SCK_3.3V3: U19.P$17, U22.15, U23.5
SCK_5V: JP3.6, JP4.3, U2.D13, U3.14
SCK_5V1: JP8.6, JP9.3, U8.D13, U10.14
SCK_5V2: JP13.6, JP14.3, U14.D13, U16.14
SCK_5V3: JP18.6, JP19.3, U20.D13, U22.14
SCL: JP3.10, U2.SCL
SCL1: JP8.10, U8.SCL
SCL2: JP13.10, U14.SCL
SCL3: JP18.10, U20.SCL
SDA: JP3.9, U2.SDA
SDA1: JP8.9, U8.SDA
SDA2: JP13.9, U14.SDA
SDA3: JP18.9, U20.SDA
SD_CS_3.3V: R5.1, U3.4, U4.2
SD_CS_3.3V1: R10.1, U10.4, U11.2
SD_CS_3.3V2: R15.1, U16.4, U17.2
SD_CS_3.3V3: R20.1, U22.4, U23.2
SD_CS_5V: JP3.1, U2.D8, U3.5
SD_CS_5V1: JP8.1, U8.D8, U10.5
SD_CS_5V2: JP13.1, U14.D8, U16.5
SD_CS_5V3: JP18.1, U20.D8, U22.5
VIN: JP5.4, U2.VIN
VIN1: JP10.4, U8.VIN
VIN2: JP15.4, U14.VIN
VIN3: JP20.4, U20.VIN
WIFI_MISO: U5.P$13, U6.2
WIFI_MISO1: U7.P$13, U12.2
WIFI_MISO2: U13.P$13, U18.2
WIFI_MISO3: U19.P$13, U24.2
WIFI_RX: JP1.2, U5.P$8
WIFI_RX1: JP6.2, U7.P$8
WIFI_RX2: JP11.2, U13.P$8
WIFI_RX3: JP16.2, U19.P$8
WIFI_TX: JP1.1, U5.P$6
WIFI_TX1: JP6.1, U7.P$6
WIFI_TX2: JP11.1, U13.P$6
WIFI_TX3: JP16.1, U19.P$6

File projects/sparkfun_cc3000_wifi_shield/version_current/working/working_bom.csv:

"Id";"Designator";"Footprint";"Quantity";"Designation";"Supplier and ref";
1;"U7,U5,U19,U13";"QFN-46_CC3000";4;"CC3000";;;
2;"R13,R2,R7,R8,R12,R17,R18,R3";"0603-RES";8;"390";;;
3;"C1,C2,C15,C23,C31,C32,C24,C16";"0805";8;"10uF";;;
4;"U15,U21,U9,U1";"SOT223";4;"LM1117";;;
5;"E$4,E$5";"FIDUCIAL-1X2";2;"";;;
6;"D3,D1,D2,D4";"LED-0603";4;"GREEN";;;
7;"JP16,JP11,JP6,JP1";"1X03";4;"Debug";;;
8;"U11,U23,U4,U17";"MICRO-SD-SOCKET-PP";4;"USD-SOCKETNEW";;;
9;"JP2,JP17,JP7,JP12";"1X08_NO_SILK";4;"";;;
10;"SJ3,SJ1,SJ2,SJ4";"SJ_3_PASTE1&2";4;"Mode";;;
11;"C18,C11,C26,C27,C5,C19,C4,C10";"0805";8;"1uF";;;
12;"R6,R16,R11,R1";"0603-RES";4;"240";;;
13;"@HOLE4,@HOLE3,@HOLE0,@HOLE1,@HOLE5,@HOLE6,@HOLE7,@HOLE2";"";8;"";;;
14;"U16,U3,U10,U22";"SO016";4;"74HC4050";;;
15;"C20,C28,C6,C12";"0603-CAP";4;"10pF";;;
16;"C30,C7,C14,C22";"0603-CAP";4;"2.2pF";;;
17;"FID2,FID8,FID1,FID6,FID3,FID4,FID7,FID5";"FIDUCIAL-1X2";8;"FIDUCIAL1X2";;;
18;"JP18,JP3,JP13,JP8";"1X10_NO_SILK";4;"M10NO_SILK";;;
19;"STANDOFF4,STANDOFF1,STANDOFF6,STANDOFF2,STANDOFF7,STANDOFF8,STANDOFF3,STANDOFF5";"STAND-OFF";8;"STAND-OFF";;;
20;"L3,L1,L7,L5";"0603";4;"DNP";;;
21;"C25,C9,C17,C3";"0603-CAP";4;"0.1uF";;;
22;"U20,U2,U14,U8";"UNO_R3_SHIELD_NOLABELS";4;"ARDUINO_R3_SHIELDNOLABELS";;;
23;"R5,R15,R10,R20,R14,R9,R4,R19";"0603-RES";8;"10k";;;
24;"S3,S2,S1,S4";"TACTILE_SWITCH_SMD";4;"RESET";;;
25;"AE2,AE1,AE3,AE4";"ANTENNA-CHIP_2500AT44M0400";4;"ANTENNA22500AT44M0400";;;
26;"JP20,JP15,JP10,JP5";"1X04";4;"";;;
27;"J3,J4,J2,J1";"U.FL";4;"U.FL";;;
28;"C29,C21,C13,C8";"0603-CAP";4;"DNP";;;
29;"L6,L8,L4,L2";"0603";4;"2.2nH";;;
30;"JP4,JP9,JP14,JP19";"2X3";4;"AVR_SPI_PRG_6PTH";;;
31;"U6,U18,U24,U12";"SOT23-5";4;"74AHC1G125";;;
32;"LOGO9,LOGO12,LOGO6,LOGO3";"SFE-LOGO-FLAME";4;"LOGO-SFESK";;;
33;"LOGO4,LOGO1,LOGO10,LOGO7";"OSHW-LOGO-S";4;"OSHW-LOGOS";;;
34;"E$1";"FIDUCIAL-1.5X3";1;"";;;
35;"LOGO11,LOGO2,LOGO5,LOGO8";"SFE-NEW-WEBLOGO";4;"LOGO-SFENEW";;;

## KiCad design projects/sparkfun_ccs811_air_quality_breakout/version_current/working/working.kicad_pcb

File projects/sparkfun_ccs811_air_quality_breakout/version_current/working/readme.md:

# CCS811_Air_Quality_Breakout by sparkfun  
This is a harvested standardized copy of a project from github.  
The original project can be found at:  
https://github.com/sparkfun/CCS811_Air_Quality_Breakout  
Please consult that link for additional, details, files, and license information.  
Note: It was auto harvested and if the original repo had more than one board file or anything out of the ordinary the files here are likely not representative.

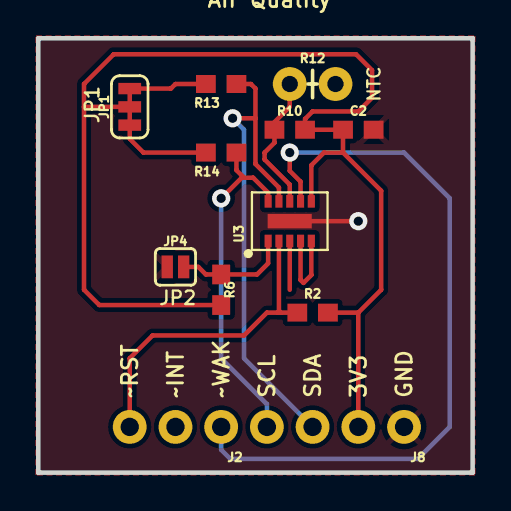
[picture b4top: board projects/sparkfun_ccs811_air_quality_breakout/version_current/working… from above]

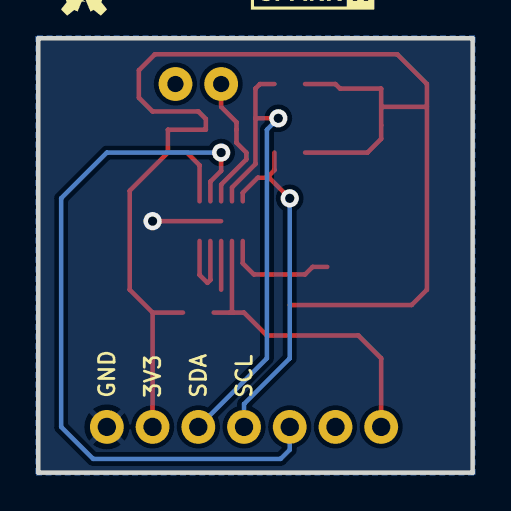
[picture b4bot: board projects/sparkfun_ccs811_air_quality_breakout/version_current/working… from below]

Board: 2 copper layers, 24.1 x 24.1 mm, 15 parts (2 on the bottom side), 12 nets.

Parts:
C2: 1.0uF; 0603
FRAME1: FRAME-LETTER; CREATIVE_COMMONS
J2: 1X03_NO_SILK
J8: 1X04_NO_SILK
JP1: SMT-JUMPER_3_2-NC_TRACE_SILK
JP4: SMT-JUMPER_2_NO_SILK
LOGO4: OSHW-LOGOS; OSHW-LOGO-S
R2, R13, R14: 4.7k; 0603
R6: 100k; 0603
R10: 10k; 0603
R12: DNP; AXIAL-0.1
U3: CCS811SKINNY; LGA10-MILLABLE
U$1: SPARKX-LOGO3; SPARKX-SMALL

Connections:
3.3V: C2.1, J8.2, JP1.2, R2.2, R6.2, R10.2, U3.6
AUX: R10.1, R12.P$1, U3.8
CCS811_ADDR: JP4.2, R6.1, U3.1
GND: C2.2, J8.1, JP4.1, U3.EP
unnamed: JP1.3, R13.2
unnamed: JP1.1, R14.2
NTC_SENSE: R12.P$2, U3.4, U3.5
SCL: J8.4, R14.1, U3.10
SDA: J8.3, R13.1, U3.9
~INT: J2.2, U3.3
~RST: J2.3, R2.1, U3.2
~WAKE: J2.1, U3.7

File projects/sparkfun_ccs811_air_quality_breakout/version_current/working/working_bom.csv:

Row,Description,Part,References,Value,Footprint,Quantity Per PCB,Status,Datasheet,PROD_ID
1,,1.0UF-0603-16V-10%,C2,1.0UF-0603-16V-10%,0603,1, ,,
2,,FRAME-LETTER,FRAME1,FRAME-LETTER,CREATIVE_COMMONS,1, ,,
3,,CONN_031X03_NO_SILK,J2,CONN_031X03_NO_SILK,1X03_NO_SILK,1, ,,
4,,I2C_STANDARD_NO_SILK,J8,I2C_STANDARD_NO_SILK,1X04_NO_SILK,1, ,,
5,,JUMPER-SMT_2_NO_SILK,JP4,JUMPER-SMT_2_NO_SILK,SMT-JUMPER_2_NO_SILK,1, ,,
6,,JUMPER-SMT_3_2-NC_TRACE_SILK,JP1,JUMPER-SMT_3_2-NC_TRACE_SILK,SMT-JUMPER_3_2-NC_TRACE_SILK,1, ,,
7,,OSHW-LOGOS,LOGO4,OSHW-LOGOS,OSHW-LOGO-S,1, ,,
8,,100KOHM-0603-1/10W-1%,R6,100KOHM-0603-1/10W-1%,0603,1, ,,
9,,10KOHM-0603-1/10W-1%,R10,10KOHM-0603-1/10W-1%,0603,1, ,,
10,,4.7KOHM-0603-1/10W-1%,R2 R13 R14,4.7KOHM-0603-1/10W-1%,0603,3, ,,
11,,NTC-THERMISTOR-AXIAL-0.1,R12,NTC-THERMISTOR-AXIAL-0.1,AXIAL-0.1,1, ,,N/A
12,,CCS811SKINNY,U3,CCS811SKINNY,LGA10-MILLABLE,1, ,,
13,,SPARKX-LOGO3,U$1,SPARKX-LOGO3,SPARKX-SMALL,1, ,,





Project info:
Schematic:,working
Variant:,default
Revision:,
Date:,2023-08-06_12-56-00
KiCad Version:,7.0.6-7.0.6~ubuntu22.04.1
Statistics:
Component Groups:,13
Component Count:,15 (0 SMD/ 0 THT)
Fitted Components:,15 (0 SMD/ 0 THT)
Number of PCBs:,1
Total Components:,15

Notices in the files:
projects/sparkfun_breadboard_power_supply_stick_5v_3_3v/version_current/working/working.kicad_sch:
Released under the Creative Commons
projects/sparkfun_buck_boost/version_current/working/working.kicad_sch:
https://creativecommons.org/licenses/by-sa/4.0
parts and their libraries:
Released under the Creative Commons Attribution Share-Alike 4.0 License
